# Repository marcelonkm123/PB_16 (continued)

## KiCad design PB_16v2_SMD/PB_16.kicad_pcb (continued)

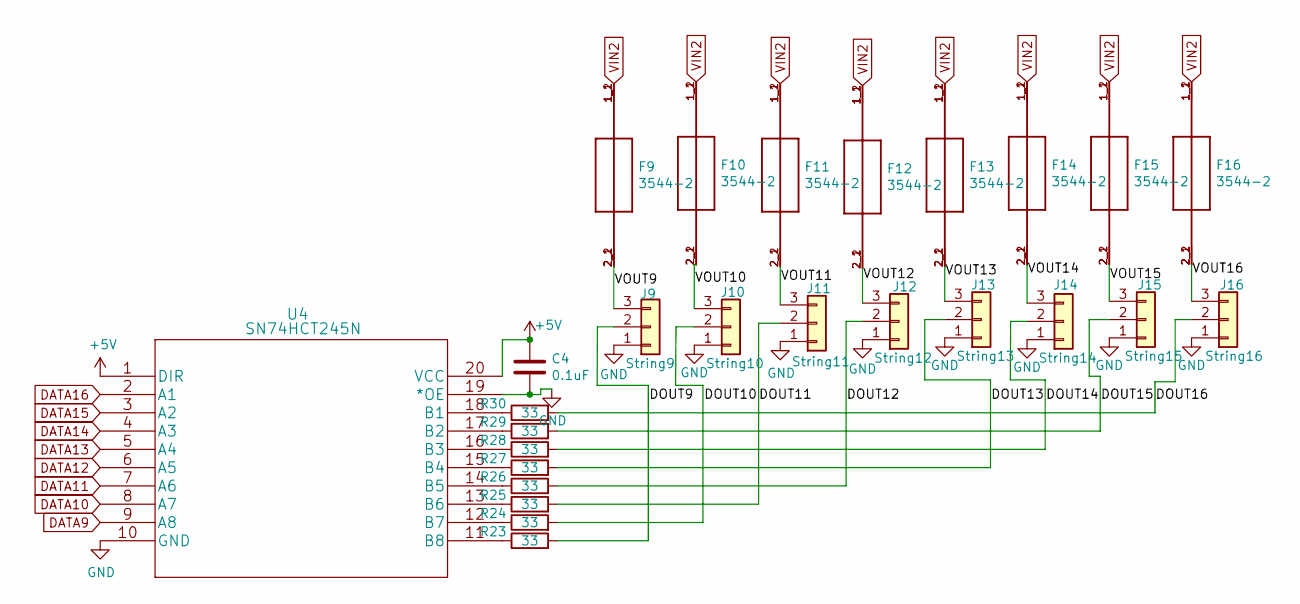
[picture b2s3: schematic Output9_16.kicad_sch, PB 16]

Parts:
C4: 0.1uF; C_0805_2012Metric_Pad1.15x1.40mm_HandSolder; MPN CL21F104ZBCNNNC; Digi-Key_PN 1276-1007-1-ND
F9, F10, F11, F12, F13, F14, F15, F16: 3544-2; FUSE_3544-2; MPN 3544-2; Digi-Key_PN 36-3544-2-ND
J9: String9; PhoenixContact_MCV_1,5_3-G-3.5_1x03_P3.50mm_Vertical; MPN 1843619/OSTTJ0311530; Digi-Key_PN 277-5737-ND/ED10555-ND
J10: String10; PhoenixContact_MCV_1,5_3-G-3.5_1x03_P3.50mm_Vertical; MPN 1843619/OSTTJ0311530; Digi-Key_PN 277-5737-ND/ED10555-ND
J11: String11; PhoenixContact_MCV_1,5_3-G-3.5_1x03_P3.50mm_Vertical; MPN 1843619/OSTTJ0311530; Digi-Key_PN 277-5737-ND/ED10555-ND
J12: String12; PhoenixContact_MCV_1,5_3-G-3.5_1x03_P3.50mm_Vertical; MPN 1843619/OSTTJ0311530; Digi-Key_PN 277-5737-ND/ED10555-ND
J13: String13; PhoenixContact_MCV_1,5_3-G-3.5_1x03_P3.50mm_Vertical; MPN 1843619/OSTTJ0311530; Digi-Key_PN 277-5737-ND/ED10555-ND
J14: String14; PhoenixContact_MCV_1,5_3-G-3.5_1x03_P3.50mm_Vertical; MPN 1843619/OSTTJ0311530; Digi-Key_PN 277-5737-ND/ED10555-ND
J15: String15; PhoenixContact_MCV_1,5_3-G-3.5_1x03_P3.50mm_Vertical; MPN 1843619/OSTTJ0311530; Digi-Key_PN 277-5737-ND/ED10555-ND
J16: String16; PhoenixContact_MCV_1,5_3-G-3.5_1x03_P3.50mm_Vertical; MPN 1843619/OSTTJ0311530; Digi-Key_PN 277-5737-ND/ED10555-ND
R23, R24, R25, R26, R27, R28, R29, R30: 33; R_0603_1608Metric_Pad0.98x0.95mm_HandSolder; MPN CN34J330CT; LCSC C23140
U4: SN74HCT245N; SN74HCT245NSR; MPN SN74HCT245NSR; Digi-Key_PN 296-15849-1-ND

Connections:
+5V: C4.1, U4.1 (DIR), U4.20 (VCC); also elsewhere on the board
/Output 9-16/DOUT12: J12.2, R26.2
/Output 9-16/DOUT13: J13.2, R27.2
/Output 9-16/DOUT15: J15.2, R29.2
/Output 9-16/DOUT16: J16.2, R30.2
/Output 9-16/VOUT9: F9.2_1 (2), F9.2_2 (2), J9.3
/Output 9-16/VOUT10: F10.2_1 (2), F10.2_2 (2), J10.3
/Output 9-16/VOUT11: F11.2_1 (2), F11.2_2 (2), J11.3
/Output 9-16/VOUT12: F12.2_1 (2), F12.2_2 (2), J12.3
/Output 9-16/VOUT13: F13.2_1 (2), F13.2_2 (2), J13.3
/Output 9-16/VOUT14: F14.2_1 (2), F14.2_2 (2), J14.3
/Output 9-16/VOUT15: F15.2_1 (2), F15.2_2 (2), J15.3
/Output 9-16/VOUT16: F16.2_1 (2), F16.2_2 (2), J16.3
DATA9: U4.9 (A8); also elsewhere on the board
DATA10: U4.8 (A7); also elsewhere on the board
DATA11: U4.7 (A6); also elsewhere on the board
DATA12: U4.6 (A5); also elsewhere on the board
DATA13: U4.5 (A4); also elsewhere on the board
DATA14: U4.4 (A3); also elsewhere on the board
DATA15: U4.3 (A2); also elsewhere on the board
DATA16: U4.2 (A1); also elsewhere on the board
GND: C4.2, J9.1, J10.1, J11.1, J12.1, J13.1, J14.1, J15.1, J16.1, U4.10 (GND), U4.19 (*OE); also elsewhere on the board
unnamed: J9.2, R23.2
unnamed: J10.2, R24.2
unnamed: J11.2, R25.2
unnamed: J14.2, R28.2
unnamed: R23.1, U4.11 (B8)
unnamed: R24.1, U4.12 (B7)
unnamed: R25.1, U4.13 (B6)
unnamed: R26.1, U4.14 (B5)
unnamed: R27.1, U4.15 (B4)
unnamed: R28.1, U4.16 (B3)
unnamed: R29.1, U4.17 (B2)
unnamed: R30.1, U4.18 (B1)
VIN2: F9.1_1 (1), F9.1_2 (1), F10.1_1 (1), F10.1_2 (1), F11.1_1 (1), F11.1_2 (1), F12.1_1 (1), F12.1_2 (1), F13.1_1 (1), F13.1_2 (1), F14.1_1 (1), F14.1_2 (1), F15.1_1 (1), F15.1_2 (1), F16.1_1 (1), F16.1_2 (1); also elsewhere on the board

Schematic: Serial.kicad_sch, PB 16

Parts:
C5, C9: 0.1uF; C_0805_2012Metric_Pad1.15x1.40mm_HandSolder; MPN CL21F104ZBCNNNC; Digi-Key_PN 1276-1007-1-ND
J20: DMX1 RJ45; RJ45_Amphenol_54602-x08_Horizontal; MPN A-2014-2-4-R; Digi-Key_PN AE10392-ND
J21: Diff Out; RJ45_Amphenol_54602-x08_Horizontal; MPN A-2014-2-4-R; Digi-Key_PN AE10392-ND
J22: DMX2; TerminalBlock_Phoenix_MKDS-1,5-4_1x04_P5.00mm_Horizontal; MPN 1729034; Digi-Key_PN 277-1238-ND
R1, R2, R11, R12, R13, R14: 120; R_0805_2012Metric_Pad1.15x1.40mm_HandSolder; MPN RC0805JR-07120RL; Digi-Key_PN 311-120ARCT-ND
SW1: DMX_LOR_Select; SW_CuK_JS202011CQN_DPDT_Straight; MPN JS202011JCQN; Digi-Key_PN CKN10723CT-ND
U5: UA9638CDR; SOIC-8_3.9x4.9mm_P1.27mm; MPN UA9638CDR; Digi-Key_PN 296-15058-1-ND
U8: AM26C31; SOIC-16_3.9x9.9mm_P1.27mm; MPN AM26C31IDR; Farnell 4975637

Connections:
+5V: C5.1, C9.1, U5.1 (VCC); also elsewhere on the board
/Serial/9V: J20.3
/Serial/DMX1+: R1.1, SW1.2 (B), U5.8 (OUTB)
/Serial/DMX1-: R1.2, SW1.5 (B), U5.7 (OUTA)
/Serial/DMX2+: J22.2, R2.1, U5.6 (OUTB)
/Serial/DMX2-: J22.3, R2.2, U5.5 (OUTA)
GND: C5.2, C9.2, J20.6, J20.7, J20.8, J22.4, U5.4 (GND); also elsewhere on the board
unnamed: J20.1, SW1.3 (C)
unnamed: J20.2, SW1.6 (C)
unnamed: J20.4, SW1.1 (A)
unnamed: J20.5, SW1.4 (A)
OUT17+: J21.1, R14.1
OUT17-: J21.2, R14.2
OUT18+: J21.3, R13.2
OUT18-: J21.6, R13.1
OUT19+: J21.5, R12.2
OUT19-: J21.4, R12.1
OUT20+: J21.7, R11.1
OUT20-: J21.8, R11.2
TXD1: U5.2 (IN); also elsewhere on the board
TXD2: U5.3 (IN); also elsewhere on the board
V_DMX: J22.1; also elsewhere on the board

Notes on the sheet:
DMX2
Differential Output
DMX1

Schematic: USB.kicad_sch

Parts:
C8: 0.1uF; C_0805_2012Metric_Pad1.15x1.40mm_HandSolder; MPN CL21F104ZBCNNNC; Digi-Key_PN 1276-1007-1-ND
FB1: 150 OHM; L_0805_2012Metric_Pad1.15x1.40mm_HandSolder; MPN MU2029-151Y; Digi-Key_PN MU2029-151YCT-ND
J19: USB; USB_A_Molex_105057_Vertical; MPN 1050570001; Digi-Key_PN WM8672-ND
R6, R7: 10K; R_0805_2012Metric_Pad1.15x1.40mm_HandSolder; MPN RNCP0805FTD10K0; Digi-Key_PN RNCP0805FTD10K0CT-ND
U6: TPS2051BDBVR; SOT-753; MPN TPS2051BDBVR; Digi-Key_PN 296-21265-1-ND
U9: TPD4S009DBVR; SOT-23-6_Handsoldering; MPN TPD4S009DBVR; Digi-Key_PN 296-23749-1-ND

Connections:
+3V3: R7.1; also elsewhere on the board
/USB/V_USB_FB: J19.1 (VBUS)
GND: C8.2, J19.4 (GND), J19.5 (Shield), R6.2, U9.2 (GND); also elsewhere on the board
USB_D+: J19.3 (D+), U9.3 (D2+); also elsewhere on the board
USB_D-: J19.2 (D-), U9.4 (D2-); also elsewhere on the board
USB_DVBUS: R6.1; also elsewhere on the board
V_USB: C8.1, U9.5 (VCC); also elsewhere on the board

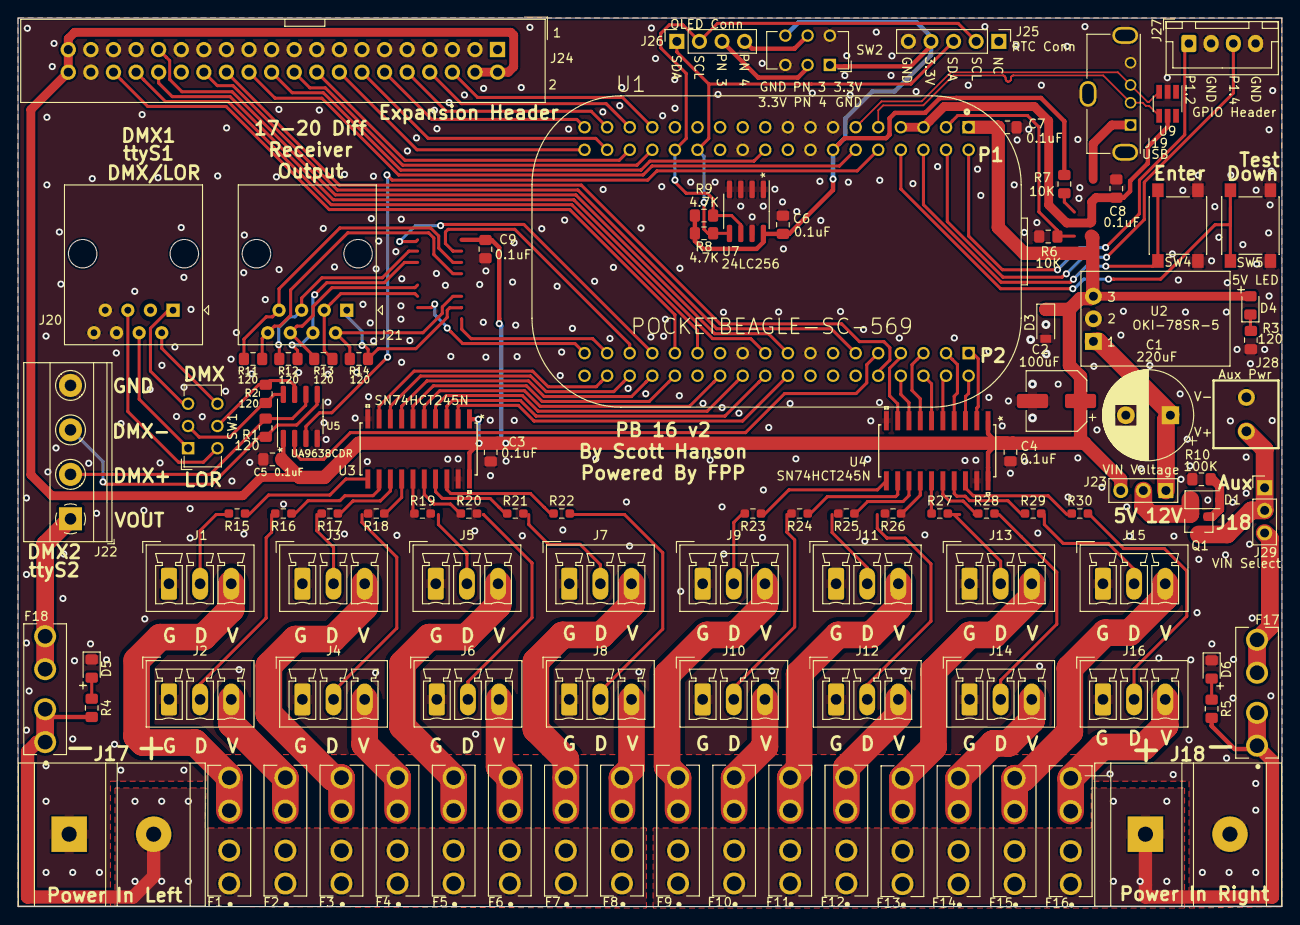
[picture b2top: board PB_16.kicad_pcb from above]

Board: 2 copper layers, 142.1 x 99.9 mm, 103 parts (0 on the bottom side), 124 nets.

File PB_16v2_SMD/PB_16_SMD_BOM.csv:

Comment,Designator,Footprint,LCSC, Digi-Key_PN, MPN, LCSC
220uF,C1,Capacitor_THT:CP_Radial_D10.0mm_P5.00mm,,1189-3684-ND,100PX220MEFC12.5X20,C88784 
100uF,C2,Capacitor_SMD:CP_Elec_6.3x5.4_Nichicon,,493-2105-1-ND,UWX1C101MCL1GB,C134723
0.1uF,"C6,C7,C3,C4,C5,C9,C8",Capacitor_SMD:C_0805_2012Metric_Pad1.15x1.40mm_HandSolder,,1276-1007-1-ND,CL21F104ZBCNNNC,C49678
Zener 10V,D1,Diode_SMD:D_SOD-123,,MMSZ5240B-FDICT-ND,MMSZ5240B-7-F,C173431
Zener 5.1V,D3,Diode_SMD:D_SOD-123,,MMSZ5231B-FDICT-ND,MMSZ5231B-7-F,C173407
5V LED,D4,LED_SMD:LED_0805_2012Metric_Pad1.15x1.40mm_HandSolder,,160-1423-1-ND,LTST-C171GKT,C2297
VIN1 LED,D5,LED_SMD:LED_0805_2012Metric_Pad1.15x1.40mm_HandSolder,,160-1423-1-ND,LTST-C171GKT,C2297
VIN2 LED,D6,LED_SMD:LED_0805_2012Metric_Pad1.15x1.40mm_HandSolder,,160-1423-1-ND,LTST-C171GKT,C2297
150 OHM,FB1,Inductor_SMD:L_0805_2012Metric_Pad1.15x1.40mm_HandSolder,,MU2029-151YCT-ND,MU2029-151Y,C1015
DMP3056L,Q1,Package_TO_SOT_SMD:SOT-23,,DMP3056L-7DICT-ND,DMP3056L-7,C150724
100K,R10,Resistor_SMD:R_0805_2012Metric_Pad1.15x1.40mm_HandSolder,,RMCF0603FT100RCT-ND,RMCF0603FT100R,C2479061
120,"R3,R2,R1,R12,R13,R14,R11",Resistor_SMD:R_0805_2012Metric_Pad1.15x1.40mm_HandSolder,,311-120ARCT-ND,RC0805JR-07120RL,C17437
1K,"R5,R4",Resistor_SMD:R_0805_2012Metric_Pad1.15x1.40mm_HandSolder,,RNCP0805FTD1K00CT-ND,RNCP0805FTD1K00,C17513
10K,"R7,R6",Resistor_SMD:R_0805_2012Metric_Pad1.15x1.40mm_HandSolder,,RNCP0805FTD10K0CT-ND,RNCP0805FTD10K0,C17414
4.7K,"R8,R9",Resistor_SMD:R_0805_2012Metric_Pad1.15x1.40mm_HandSolder,,311-4.7KARCT-ND,RC0805JR-074K7L,C17673
SN74HCT245N,"U3,U4",SN74HCT245NSR:SN74HCT245NSR,,296-15849-1-ND,SN74HCT245NSR,C133641
UA96,U5,SOIC-8_3.9x4.9x1.27P,,296-15058-1-ND,UA9638CDR,C435812
TPS2051BDBVR,U6, SOT-23-5,,, TPS2051BDBVR, C24593
24LC256,U7,Package_SO:SOIC-8_3.9x4.9mm_P1.27mm,,24LC256T-I/SNCT-ND,24LC256T-I/SN,C6482
AM26C31,U8,Package_SO:SOIC-16_3.9x9.9mm_P1.27mm,,296-24344-1-ND,AM26C31IDR,C157476
TPD4S009DBVR,U9, SOT-23-6L,,296-23749-1-ND,TPD4S009DBVR,C88032
BTNs,"SW4,SW5", KEY-SMD,,,PTS645SL50SMTR92LFS,C221877
Fuses,"F1,F2,F3,F4,F5,F6,F7,F8,F9,F10,F11,F12,F13,F14,F15,F16,F17,F18", TH-4,,, XF-506P,C492610
"SW1,SW2","SW1,SW2",9.1X3.5mm,,BBB01-SC-505-ND,JS202011CQN,C189615
RJ45,"J20,J21",RJ45-TH_R-RJ45S08P-B000_Handsolder,,,R-RJ45S08P-B000,C386763
USB,J19,,,WM8672-ND,1050570001, C586225
PwrIN,"J17, J18",CONN-TH_KF45C-9.5-2P,,ED2953-ND, KF45C-9.5-2P,C707421
Jumpers,"J23, J29", SIP-3_2.5x7.62x2.54P,,732-5316-ND,C49257,C49257
Header,J24, 2X20P,,,C9138 ,C9138 
R_Array_SIP8,"RN1,RN2,RN3,RN4",RES_ARRAY_4 RES_33_OHM_8SIP_Handsolder,,4608X-2-333LF-ND,4608X-102-333LF,
Aux_Pwr,J28,CONN-TH_2P-P3.81_KF124-3.81-2P,,277-1947-ND,WJ124-3.81-2P,C69811
DMX2,J22,CONN-TH_4P-P5.00_WJ128V-4P-5.0-14-00A,,277-1238-ND,WJ128V-5.0-4P,C192769 
RTCpins,J25,HDR-TH_5P-P2.54-V ,,,MTP125-1105S1 ,C358687 
GPIO,J27,CONN-TH_B4B-XH-A _LF_SN,,,B4B-XH-A(LF)(SN) ,C144395
RTCpins,J26,HDR-TH_5P-P2.54-V ,,,MTP125-1105S1,C358687 
5v_Reg,U2,,,102-P7805-2000-S-ND,,

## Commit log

2022-05-07 working on filling board for jlc to do the work
2022-05-26 Switching Array-res to Individual 33ohm
2022-05-26 Fixes bolding
2022-06-19 Add Diff out 9-12
2022-11-23 added fixed eeprom
